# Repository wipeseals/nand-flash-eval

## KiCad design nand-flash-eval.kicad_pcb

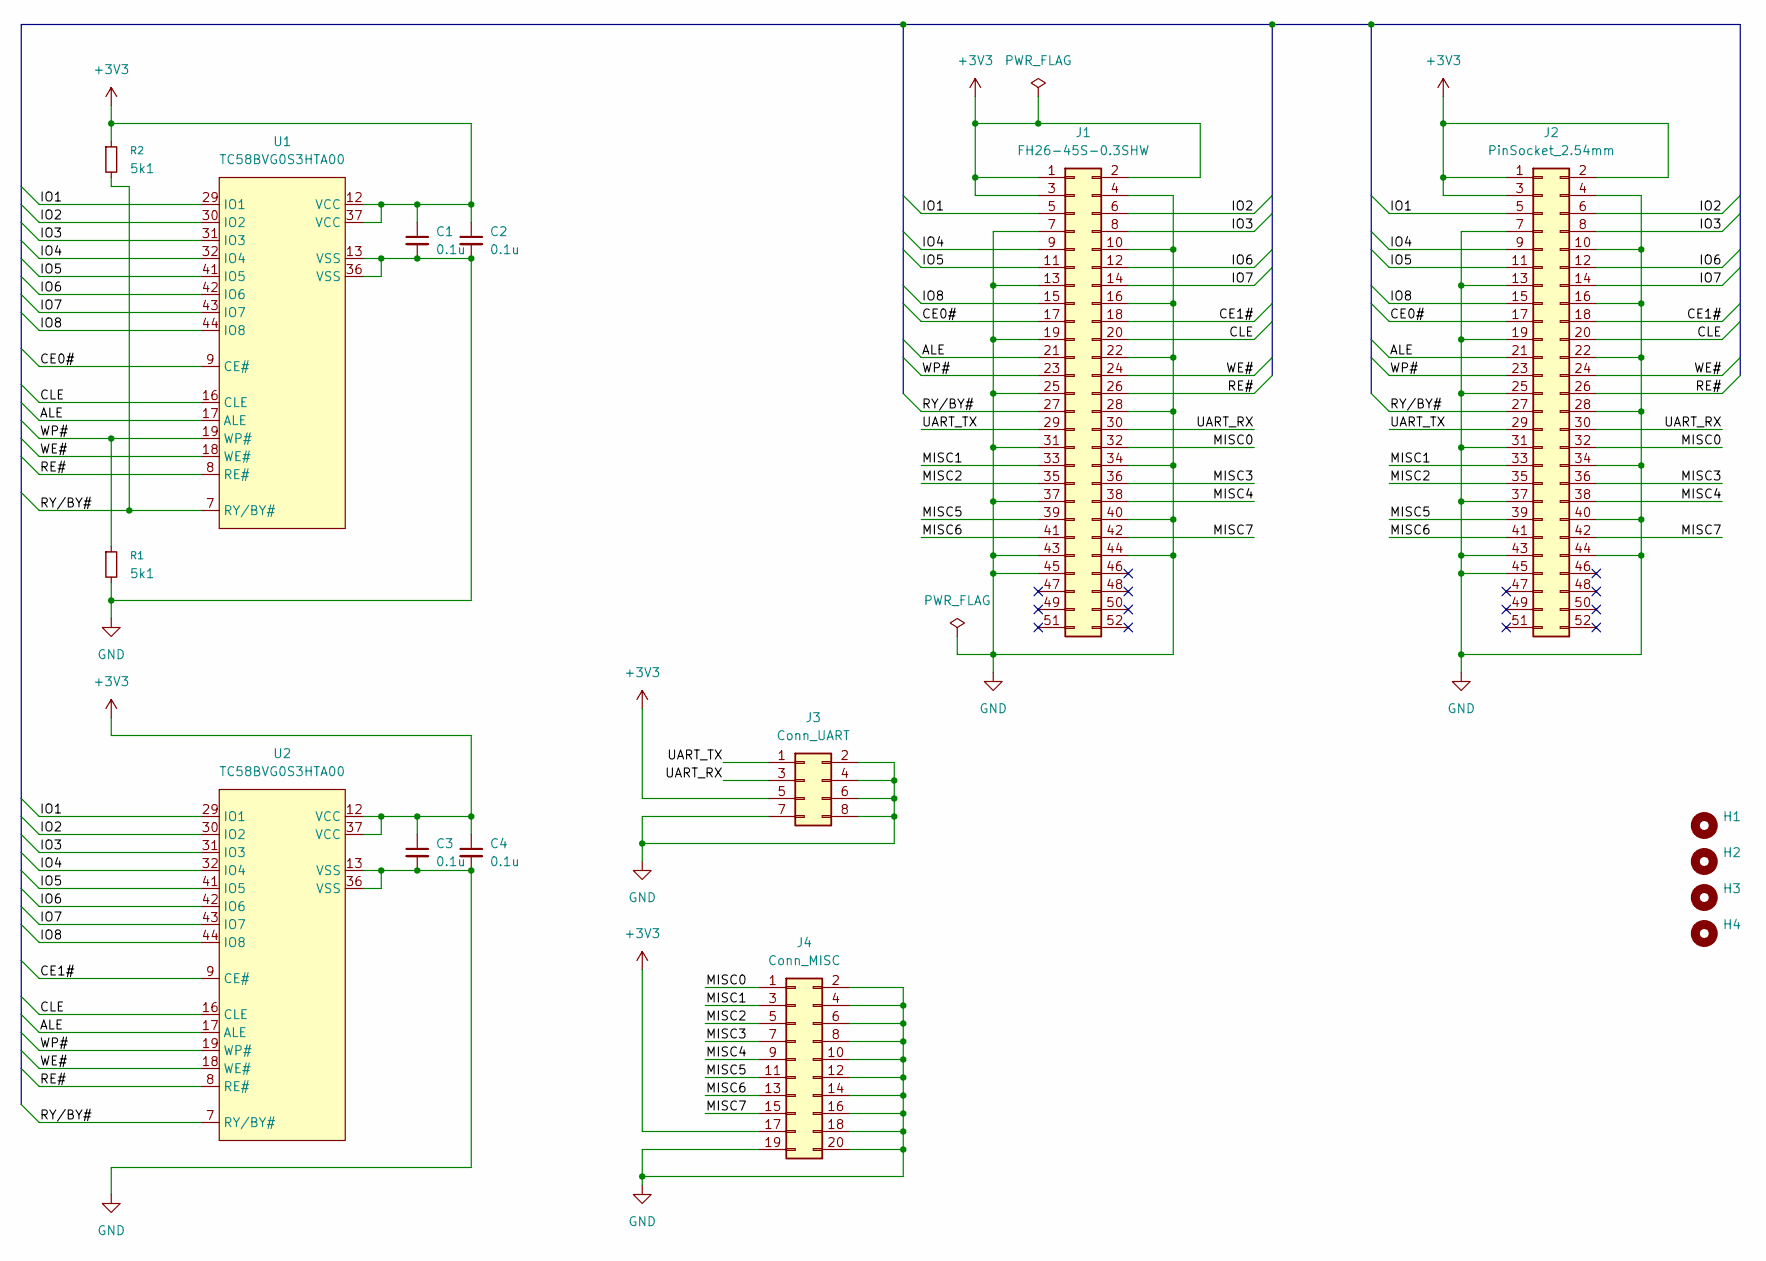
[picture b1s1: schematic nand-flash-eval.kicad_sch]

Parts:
C1, C2, C3, C4: 0.1u; C_0402_1005Metric
H1, H2, H3, H4: MountingHole; MountingHole_3.2mm_M3_ISO7380
J1: FH26-45S-0.3SHW; Hirose_FH26-45S-0.3SHW_2Rows-45Pins-1MP_P0.60mm_Horizontal
J2: PinSocket_2.54mm; PinSocket_2x25_P2.54mm_Vertical
J3: Conn_UART; PinSocket_2x04_P2.54mm_Vertical
J4: Conn_MISC; PinSocket_2x10_P2.54mm_Vertical
R1, R2: 5k1; R_0402_1005Metric
U1, U2: TC58BVG0S3HTA00; TSOP-I-48_18.4x12mm_P0.5mm

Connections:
+3V3: C1.1, C2.1, C3.1, C4.1, J1.1, J1.2, J1.3, J2.1, J2.2, J2.3, J3.5, J4.17, R2.1, U1.12 (VCC), U1.37 (VCC), U2.12 (VCC), U2.37 (VCC)
/ALE: J1.21, J2.21, U1.17 (ALE), U2.17 (ALE)
/CE0#: J1.17, J2.17, U1.9 (CE#)
/CE1#: J1.18, J2.18, U2.9 (CE#)
/CLE: J1.20, J2.20, U1.16 (CLE), U2.16 (CLE)
/IO1: J1.5, J2.5, U1.29 (IO1), U2.29 (IO1)
/IO2: J1.6, J2.6, U1.30 (IO2), U2.30 (IO2)
/IO3: J1.8, J2.8, U1.31 (IO3), U2.31 (IO3)
/IO4: J1.9, J2.9, U1.32 (IO4), U2.32 (IO4)
/IO5: J1.11, J2.11, U1.41 (IO5), U2.41 (IO5)
/IO6: J1.12, J2.12, U1.42 (IO6), U2.42 (IO6)
/IO7: J1.14, J2.14, U1.43 (IO7), U2.43 (IO7)
/IO8: J1.15, J2.15, U1.44 (IO8), U2.44 (IO8)
/MISC0: J1.32, J2.32, J4.1
/MISC1: J1.33, J2.33, J4.3
/MISC2: J1.35, J2.35, J4.5
/MISC3: J1.36, J2.36, J4.7
/MISC4: J1.38, J2.38, J4.9
/MISC5: J1.39, J2.39, J4.11
/MISC6: J1.41, J2.41, J4.13
/MISC7: J1.42, J2.42, J4.15
/RE#: J1.26, J2.26, U1.8 (RE#), U2.8 (RE#)
/RY/BY#: J1.27, J2.27, R2.2, U1.7 (RY/BY#), U2.7 (RY/BY#)
/UART_RX: J1.30, J2.30, J3.3
/UART_TX: J1.29, J2.29, J3.1
/WE#: J1.24, J2.24, U1.18 (WE#), U2.18 (WE#)
/WP#: J1.23, J2.23, R1.1, U1.19 (WP#), U2.19 (WP#)
GND: C1.2, C2.2, C3.2, C4.2, J1.4, J1.7, J1.10, J1.13, J1.16, J1.19, J1.22, J1.25, J1.28, J1.31, J1.34, J1.37, J1.40, J1.43, J1.44, J1.45, J2.4, J2.7, J2.10, J2.13, J2.16, J2.19, J2.22, J2.25, J2.28, J2.31, J2.34, J2.37, J2.40, J2.43, J2.44, J2.45, J3.2, J3.4, J3.6, J3.7, J3.8, J4.2, J4.4, J4.6, J4.8, J4.10, J4.12, J4.14, J4.16, J4.18, J4.19, J4.20, R1.2, U1.13 (VSS), U1.36 (VSS), U2.13 (VSS), U2.36 (VSS)

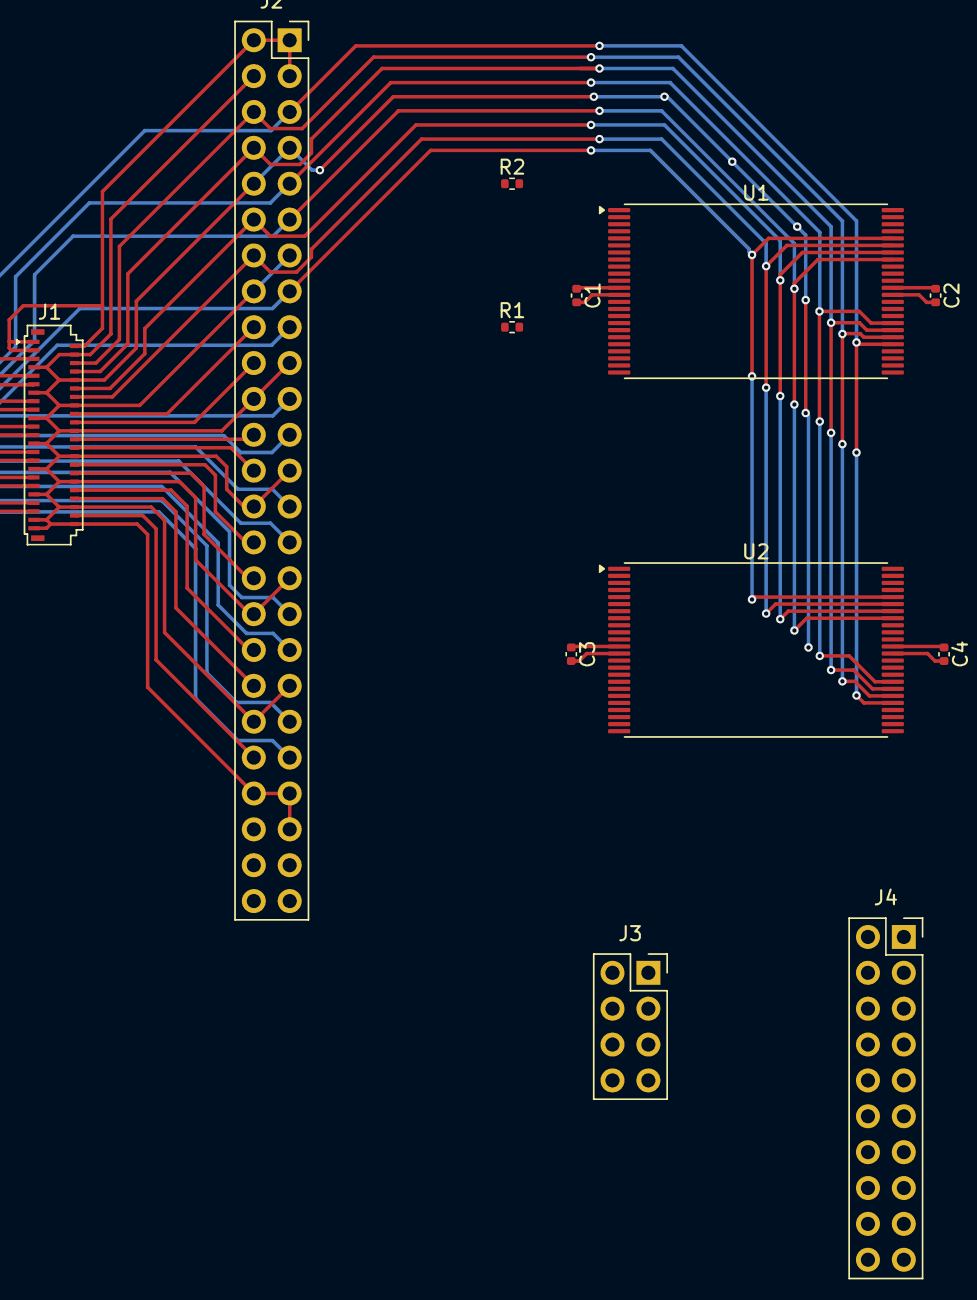
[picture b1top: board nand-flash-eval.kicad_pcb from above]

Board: 2 copper layers, 16 parts (0 on the bottom side), 28 nets.

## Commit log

2025-11-12 feat: create TC58BVG0S3HTA00 symbol
2025-11-12 chore: update .gitignore to include auto_saved_files
2025-11-12 feat: 大体書いた
2025-11-12 feat: ERC Pass
2025-11-12 fix: CE0/1
2025-11-12 feat(wip): 配線検討開始
2025-11-12 feat(wip): IO0-7配線
